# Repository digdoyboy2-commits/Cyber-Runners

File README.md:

# Cyber-Runners
Hey! This is Cyber-Runners, a custom handheld arcade console I built using a Raspberry Pi Pico. I designed the entire schematic and PCB layout from scratch in KiCad. The board features a 0.96-inch OLED display header connected to I2C0 (GPIO0 and GPIO1), four tactile push buttons for game controls, and three status LEDs for visual feedback. Everything is powered directly through the Pico's Micro-USB port.

The core KiCad source files—including the schematic, PCB layout, and project configurations—are included in this repository. Once the bare PCB is fabricated, the board is assembled by soldering the Pico, header socket for the OLED screen, push buttons, resistors, and LEDs. The console is designed to be programmed using CircuitPython or C++ to handle button inputs and render graphics on the display.

Pictures 

PCB Layout & Silkscreen

---

Electrical Schematic

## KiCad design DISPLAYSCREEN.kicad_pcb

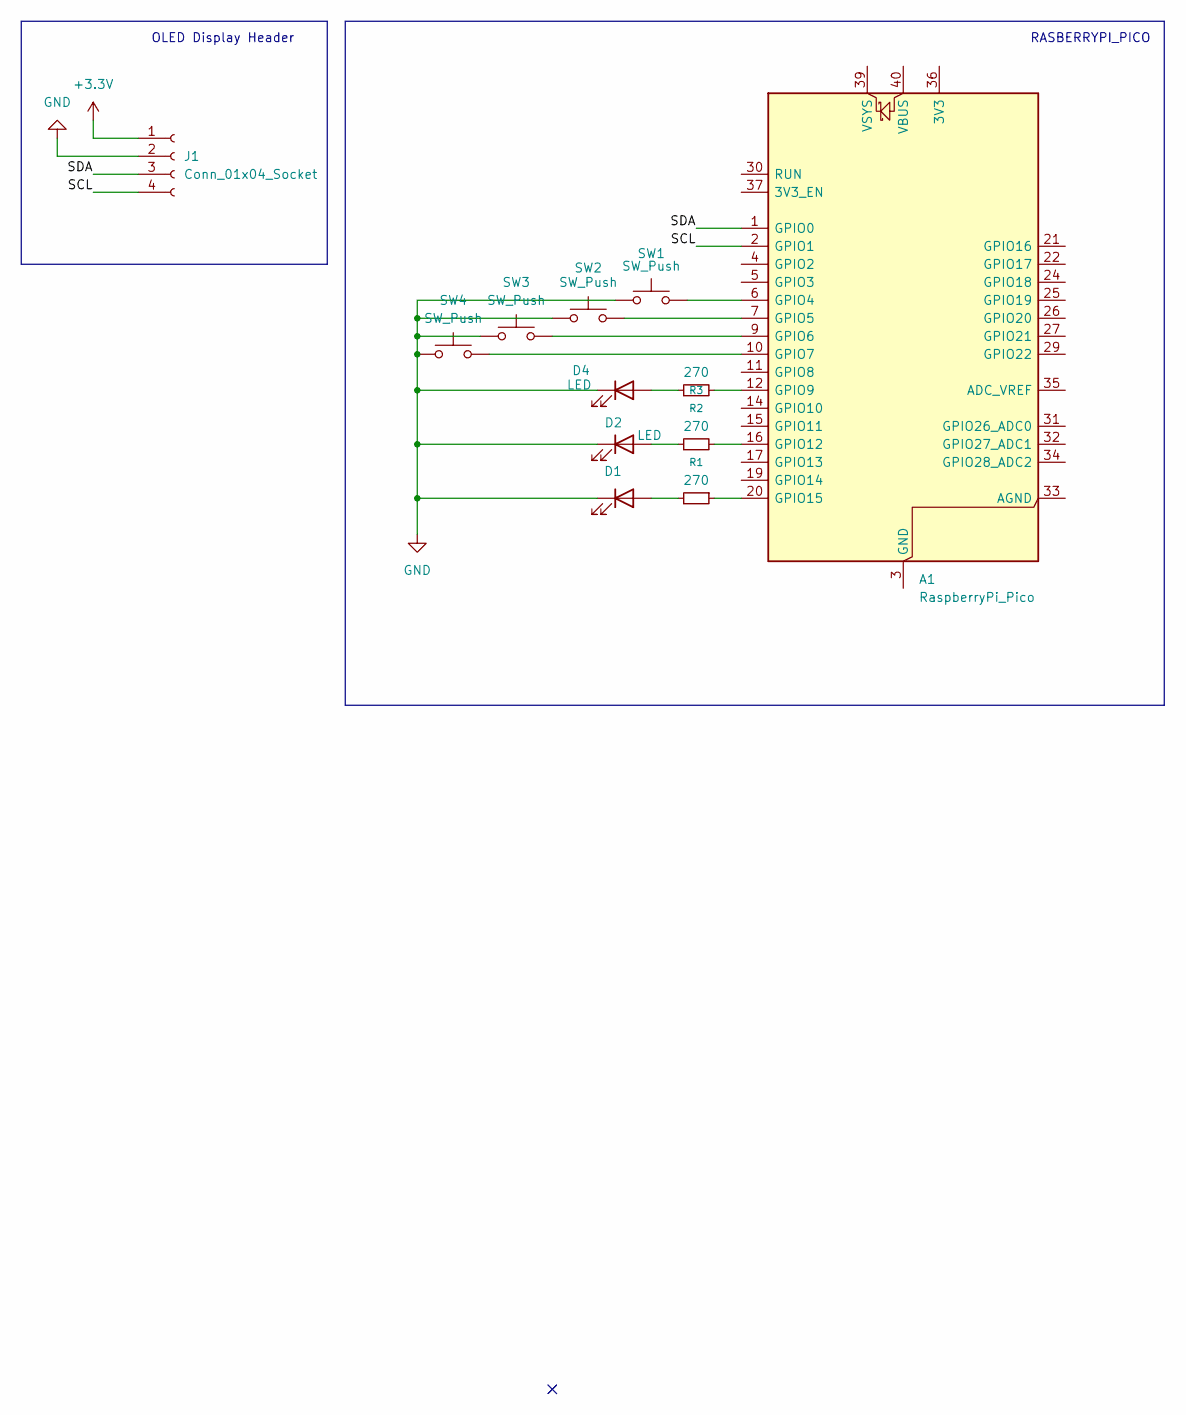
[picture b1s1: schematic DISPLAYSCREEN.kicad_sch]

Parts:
A1: RaspberryPi_Pico; RaspberryPi_Pico_Common_THT
D1, D2, D4: LED; LED_D5.0mm
J1: Conn_01x04_Socket; PinHeader_1x04_P2.54mm_Vertical
R1, R2, R3: 270; R_Axial_DIN0207_L6.3mm_D2.5mm_P7.62mm_Horizontal
SW1, SW2, SW3, SW4: SW_Push; SW_PUSH_6mm

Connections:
+3.3V: J1.1
/SCL: A1.2 (GPIO1), J1.4
/SDA: A1.1 (GPIO0), J1.3
GND: D1.1 (K), D2.1 (K), D4.1 (K), J1.2, SW1.1, SW2.1, SW3.1, SW4.1
unnamed: A1.3 (GND), A1.8 (GND), A1.13 (GND), A1.18 (GND), A1.23 (GND), A1.28 (GND), A1.38 (GND)
unnamed: A1.6 (GPIO4), SW1.2
unnamed: A1.7 (GPIO5), SW2.2
unnamed: A1.9 (GPIO6), SW3.2
unnamed: A1.10 (GPIO7), SW4.2
unnamed: A1.12 (GPIO9), R3.2
unnamed: A1.16 (GPIO12), R2.2
unnamed: A1.20 (GPIO15), R1.1
unnamed: D1.2 (A), R1.2
unnamed: D2.2 (A), R2.1
unnamed: D4.2 (A), R3.1

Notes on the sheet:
OLED Display Header
RASBERRYPI_PICO

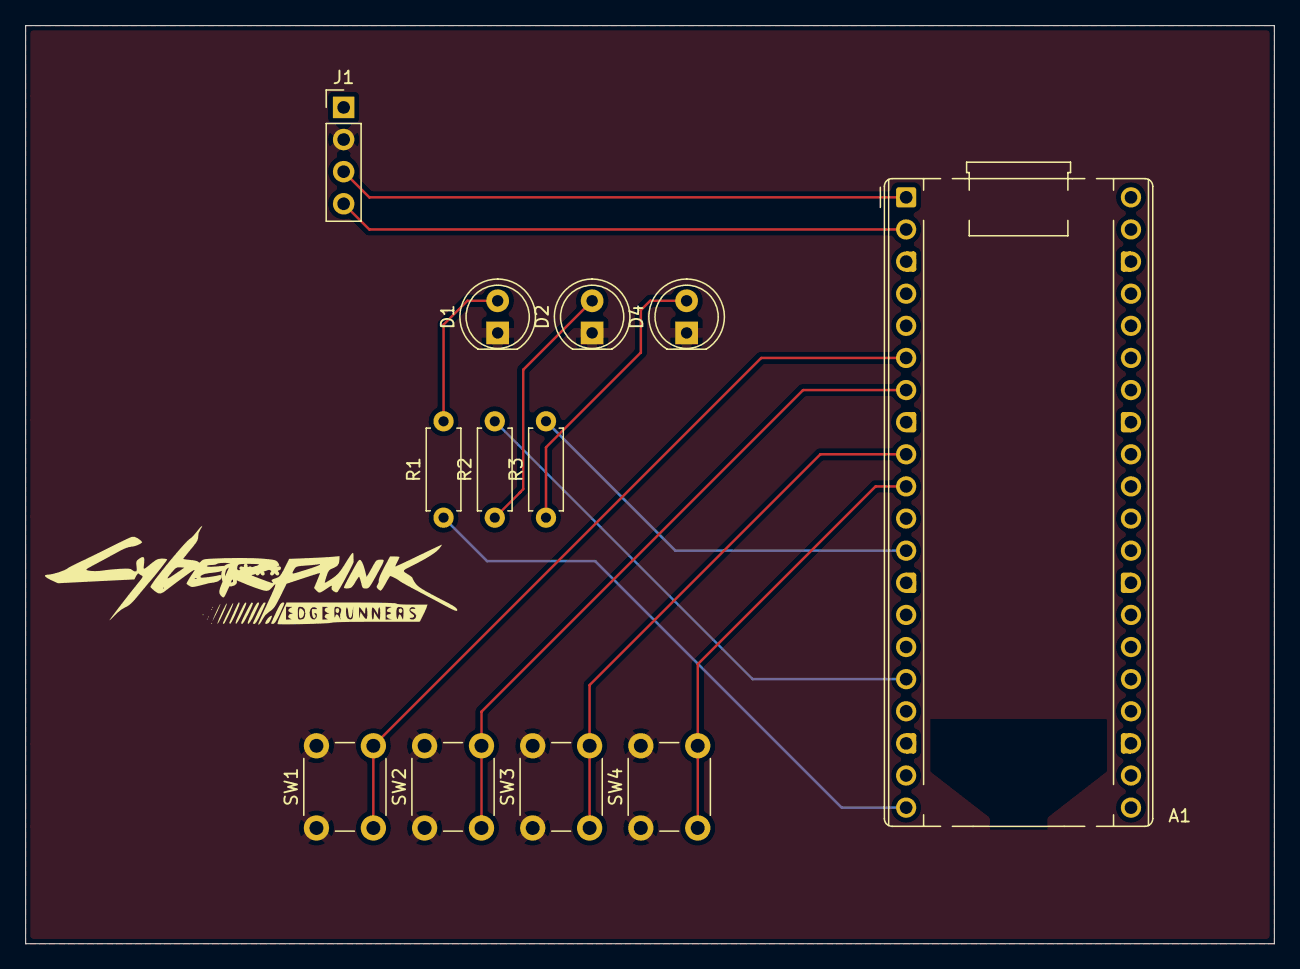
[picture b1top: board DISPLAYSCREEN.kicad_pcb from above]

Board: 2 copper layers, 98.8 x 72.6 mm, 12 parts (0 on the bottom side), 14 nets.
